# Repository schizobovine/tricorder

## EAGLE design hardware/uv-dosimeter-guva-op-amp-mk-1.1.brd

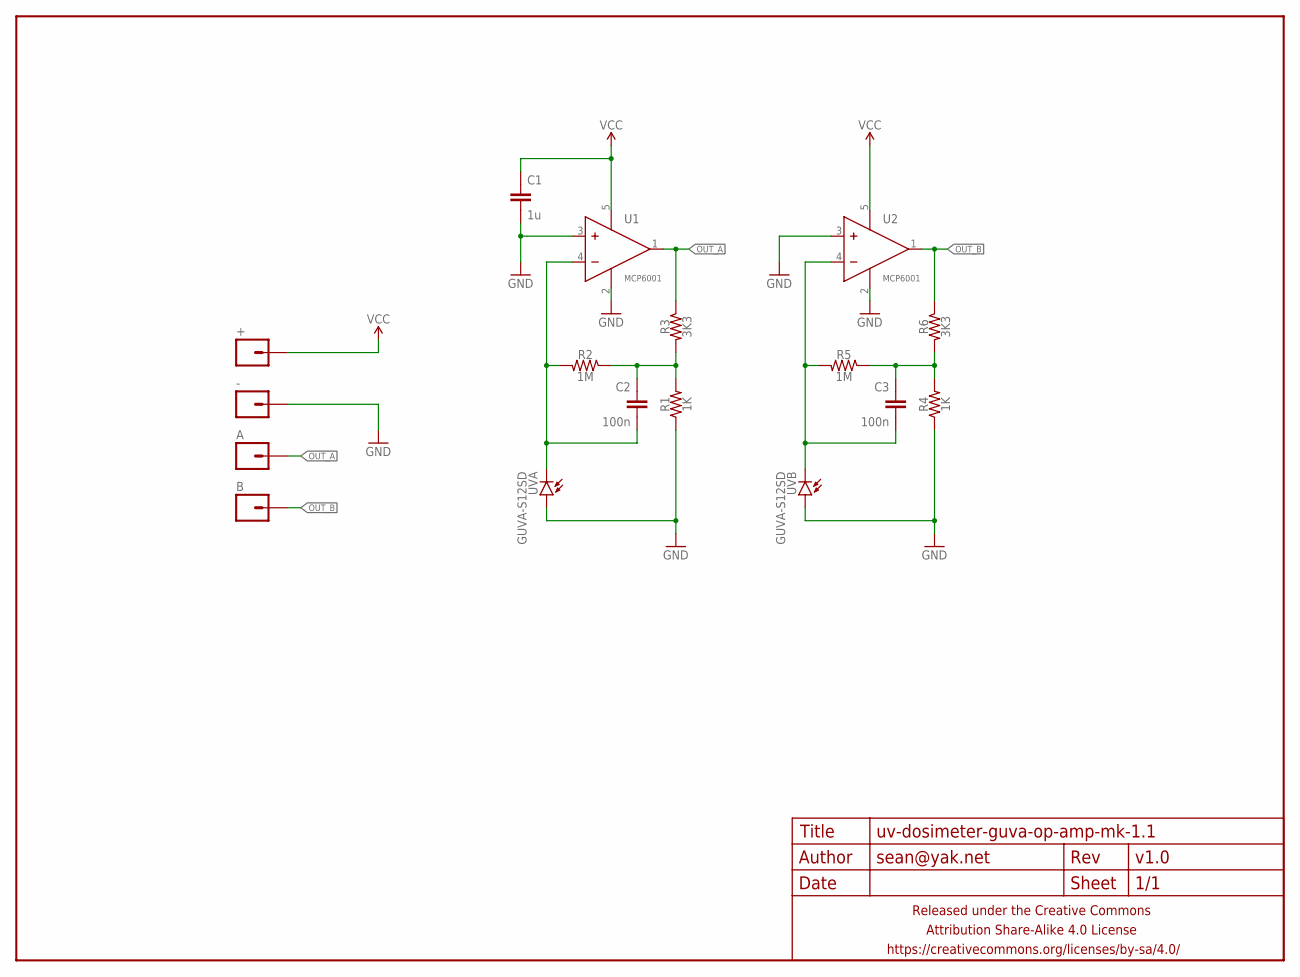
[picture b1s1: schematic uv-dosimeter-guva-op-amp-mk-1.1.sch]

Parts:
+: M01PTH; 1X01
-: M01PTH; 1X01
A: M01PTH; 1X01
B: M01PTH; 1X01
C1: 1u; C0603
C2, C3: 100n; C0603
FRAME1: FRAME-LETTERNO_PACKAGE; DUMMY
R1, R4: 1K; R0603
R2, R5: 1M; R0603
R3, R6: 3K3; R0603
U1, U2: MCP6001; SOT23-5
UVA: GUVA-S12SD; LED3528
UVB: GUVA-S12SD; LED3528

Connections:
GND: -.1, C1.2, R1.1, R4.1, U1.2 (V-), U1.3 (IN+), U2.2 (V-), U2.3 (IN+), UVA.A, UVB.A
unnamed: C2.1, R1.2, R2.1, R3.2
unnamed: C3.1, R4.2, R5.1, R6.2
NEG_FEED_A: C2.2, R2.2, U1.4 (IN-), UVA.K (C)
NEG_FEED_B: C3.2, R5.2, U2.4 (IN-), UVB.K (C)
OUT_A: A.1, R3.1, U1.1 (OUT)
OUT_B: B.1, R6.1, U2.1 (OUT)
VCC: +.1, C1.1, U1.5 (V+), U2.5 (V+)

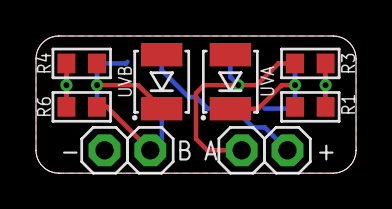
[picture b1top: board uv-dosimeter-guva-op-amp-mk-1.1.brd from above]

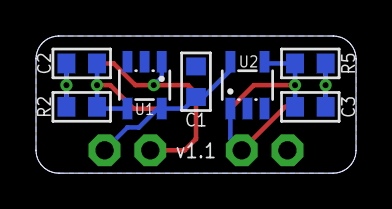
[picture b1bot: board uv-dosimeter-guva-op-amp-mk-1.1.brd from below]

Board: 2 copper layers, 17.8 x 7.6 mm, 18 parts (8 on the bottom side), 8 nets.

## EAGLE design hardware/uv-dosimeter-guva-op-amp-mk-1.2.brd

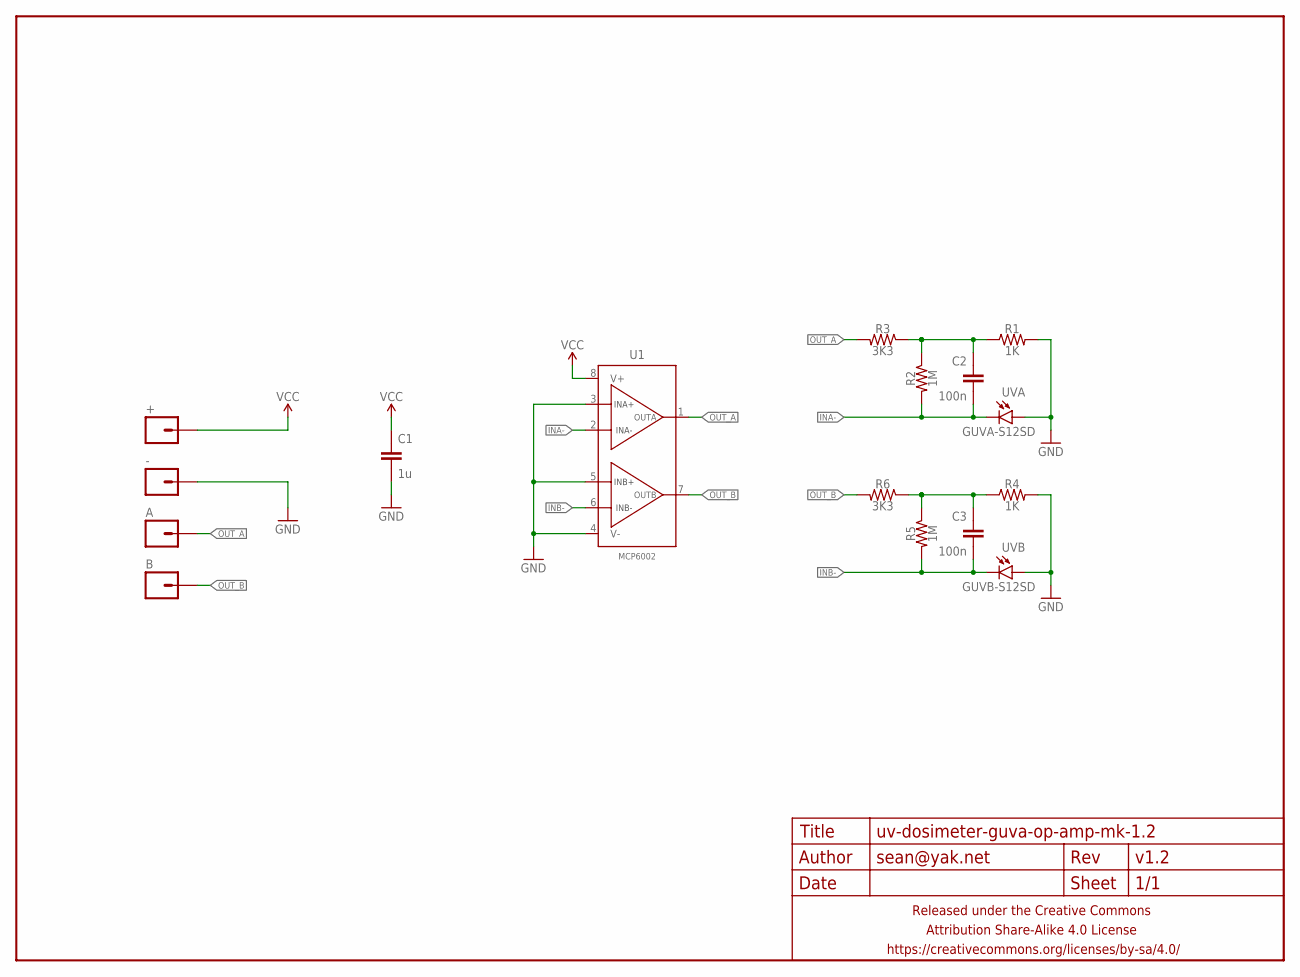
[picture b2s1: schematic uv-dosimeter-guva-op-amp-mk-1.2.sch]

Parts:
+: M01PTH; 1X01
-: M01PTH; 1X01
A: M01PTH; 1X01
B: M01PTH; 1X01
C1: 1u; C0603
C2, C3: 100n; C0603
FRAME1: FRAME-LETTERNO_PACKAGE; DUMMY
R1, R4: 1K; R0603
R2, R5: 1M; R0603
R3, R6: 3K3; R0603
U1: MCP6002; SO08
UVA: GUVA-S12SD; LED3528
UVB: GUVB-S12SD; LED3528

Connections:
GND: -.1, C1.2, R1.2, R4.2, U1.3 (INA+), U1.4 (V-), U1.5 (INB+), UVA.A, UVB.A
INA-: C2.2, R2.2, U1.2 (INA-), UVA.K (C)
INB-: C3.2, R5.2, U1.6 (INB-), UVB.K (C)
unnamed: C2.1, R1.1, R2.1, R3.1
unnamed: C3.1, R4.1, R5.1, R6.1
OUT_A: A.1, R3.2, U1.1 (OUTA)
OUT_B: B.1, R6.2, U1.7 (OUTB)
VCC: +.1, C1.1, U1.8 (V+)

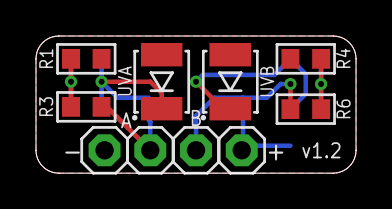
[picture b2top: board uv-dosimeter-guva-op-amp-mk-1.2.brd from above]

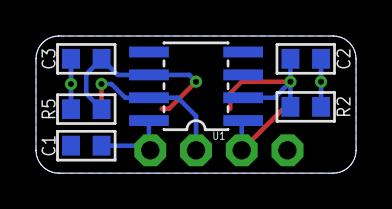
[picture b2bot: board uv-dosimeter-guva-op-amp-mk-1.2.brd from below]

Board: 2 copper layers, 17.8 x 7.6 mm, 17 parts (7 on the bottom side), 8 nets.

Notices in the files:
parts and their libraries:
A_butts: Released under the Creative Commons Attribution Share-Alike 4.0 License
A_butts: https://creativecommons.org/licenses/by-sa/4.0
A_butts: Released under the Creative Commons
